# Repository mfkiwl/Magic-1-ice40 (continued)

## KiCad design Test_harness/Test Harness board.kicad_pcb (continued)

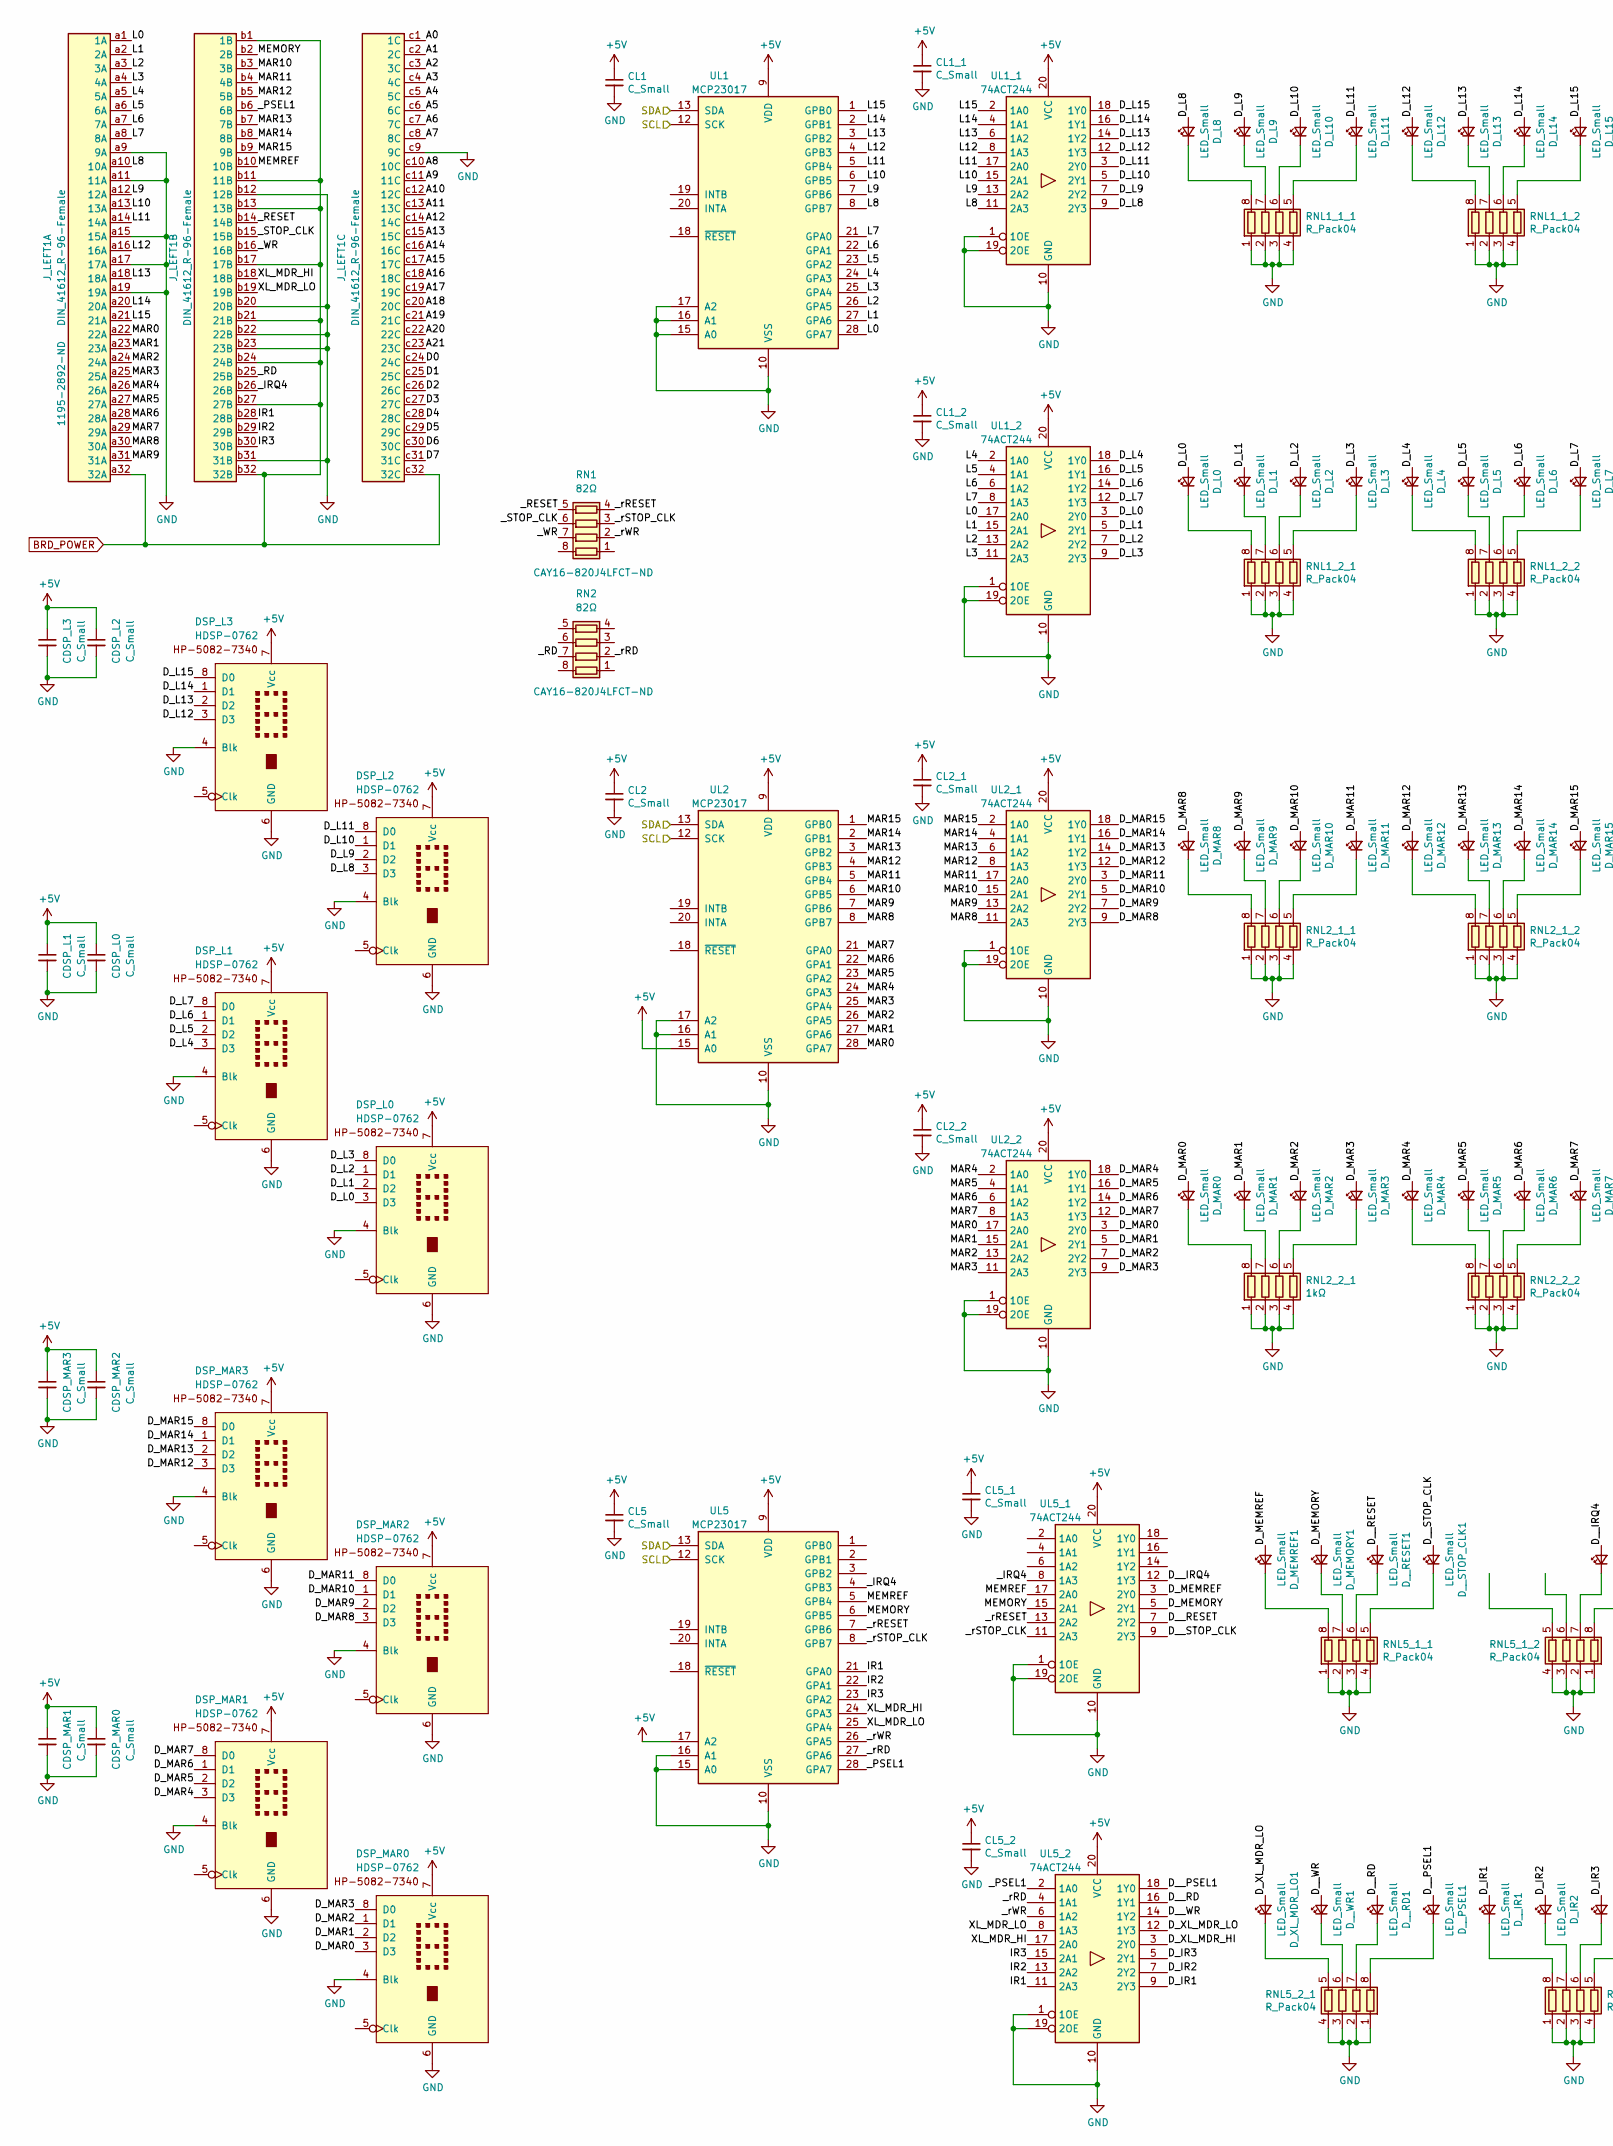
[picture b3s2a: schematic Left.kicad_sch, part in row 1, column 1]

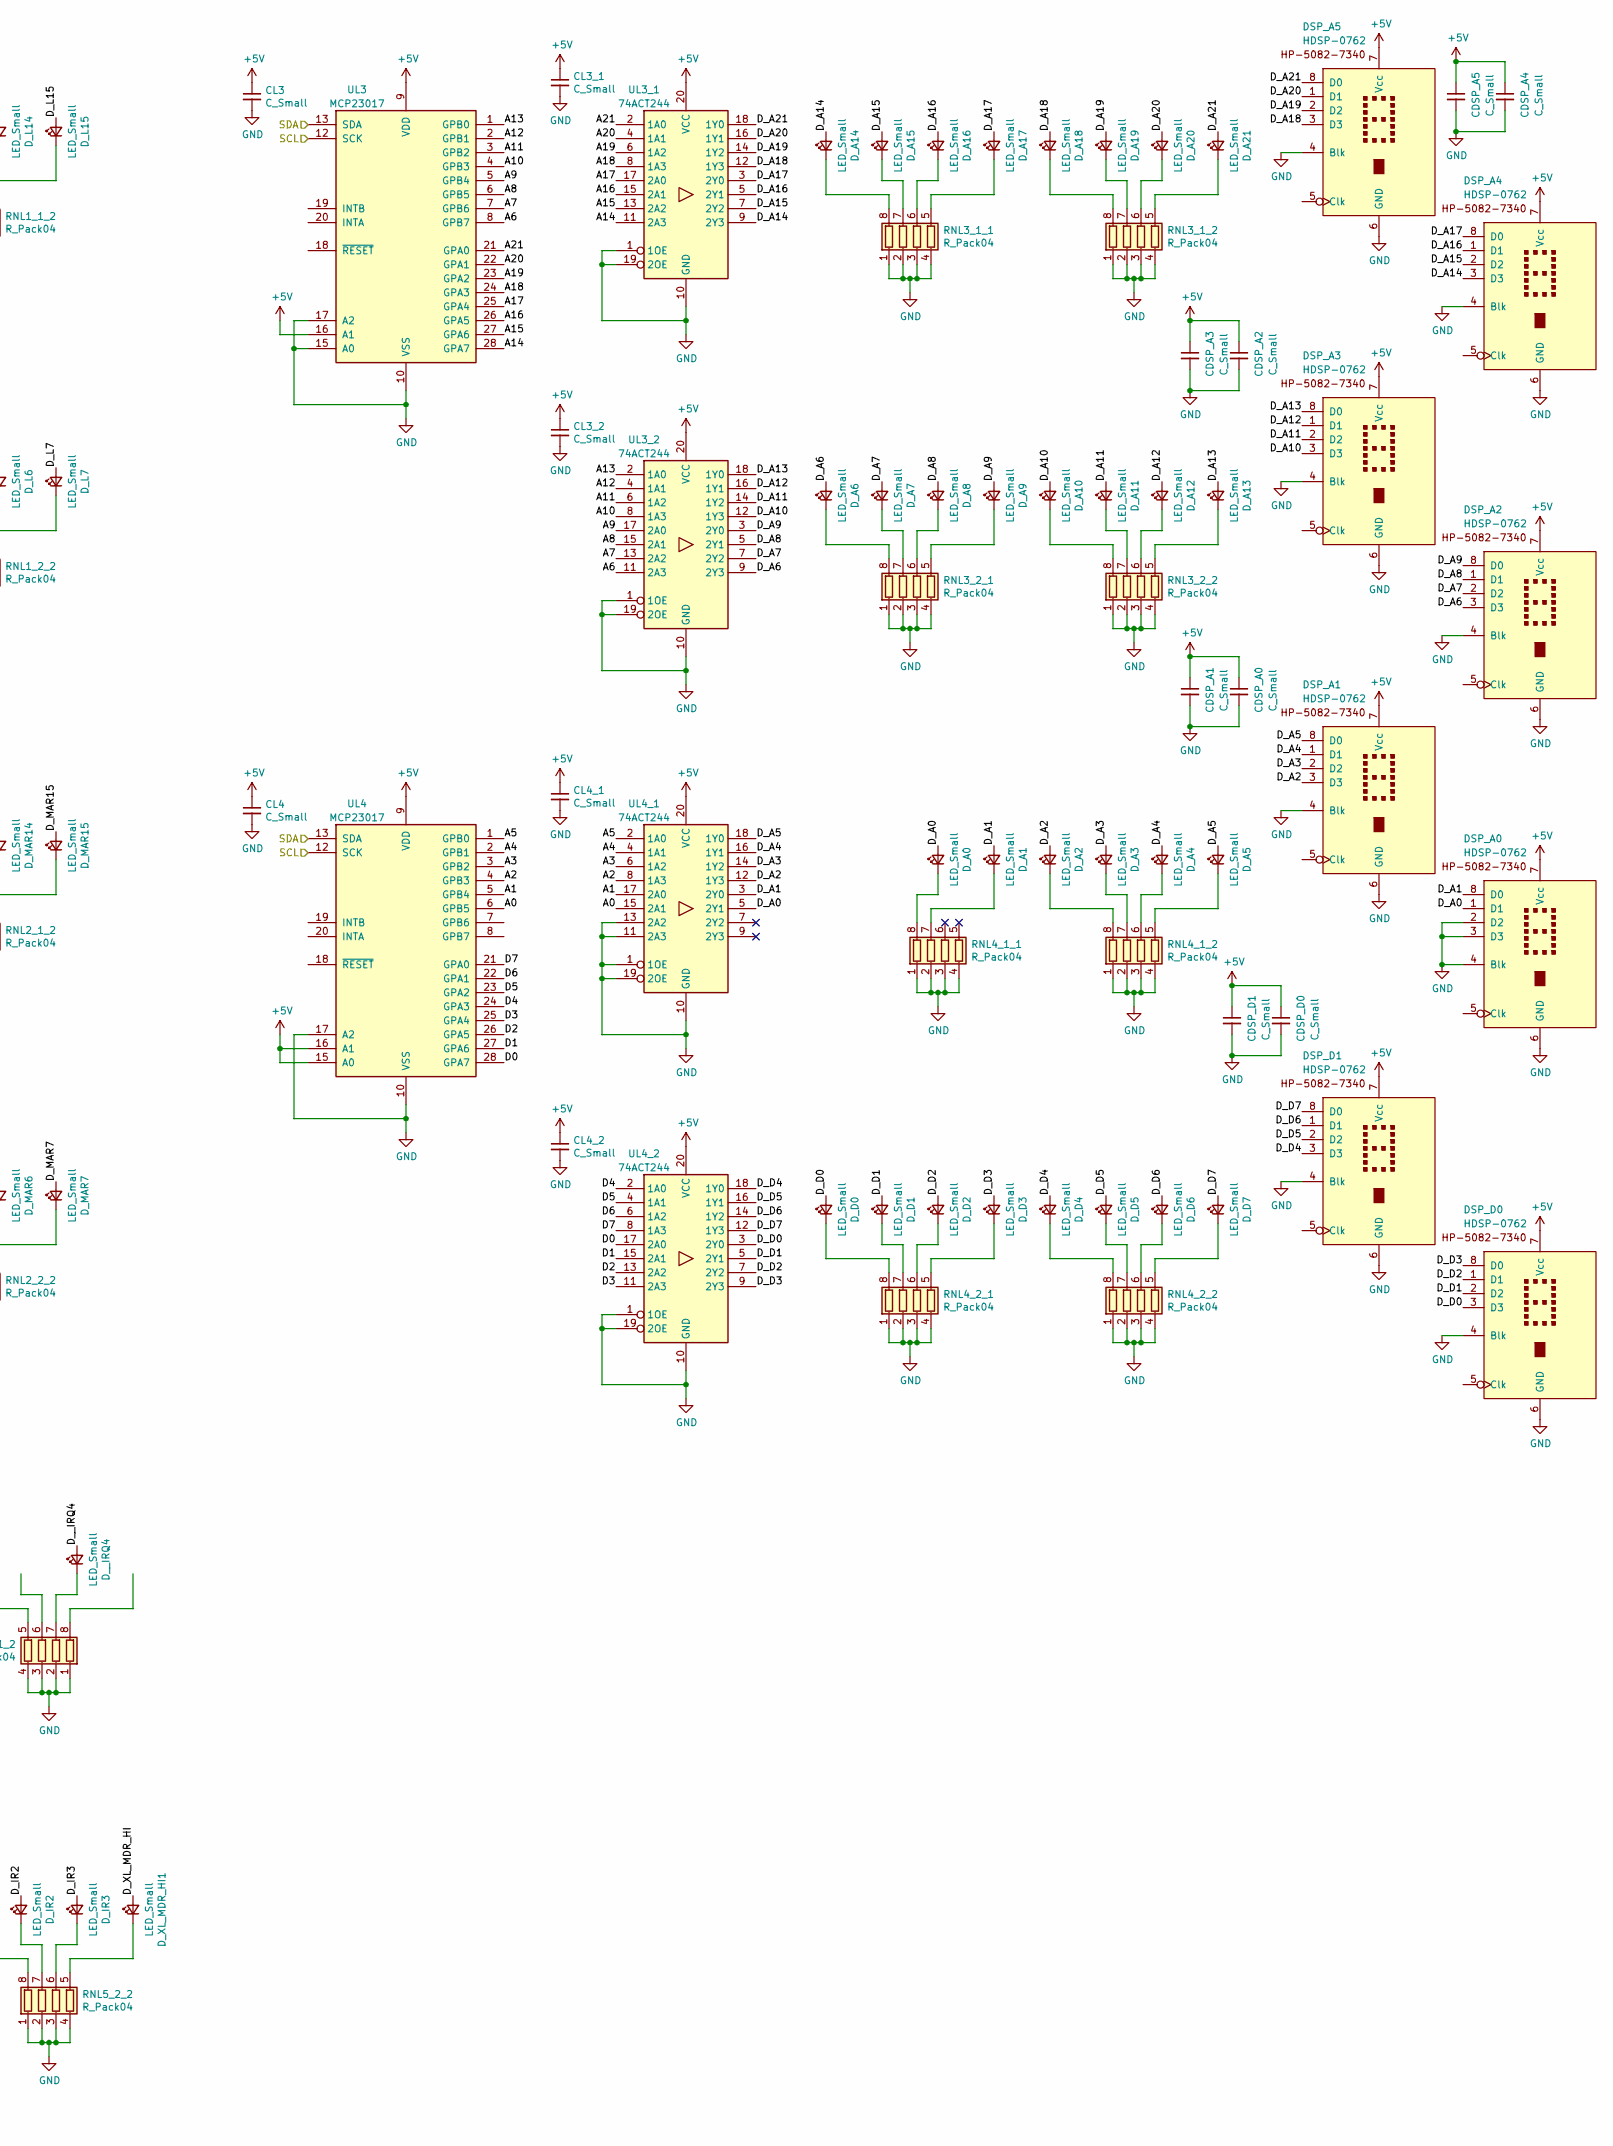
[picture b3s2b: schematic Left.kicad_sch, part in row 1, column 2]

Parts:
CDSP_A0, CDSP_A1, CDSP_A2, CDSP_A3, CDSP_A4, CDSP_A5: C_Small; C_0805_2012Metric
CDSP_D0, CDSP_D1: C_Small; C_0805_2012Metric
CDSP_L0, CDSP_L1, CDSP_L2, CDSP_L3: C_Small; C_0805_2012Metric
CDSP_MAR0, CDSP_MAR1, CDSP_MAR2, CDSP_MAR3: C_Small; C_0805_2012Metric
CL1, CL1_1, CL1_2, CL2, CL2_1, CL2_2, CL3, CL3_1, CL3_2, CL4, CL4_1, CL4_2, CL5, CL5_1, CL5_2: C_Small; C_0805_2012Metric
DSP_A0, DSP_A1, DSP_A2, DSP_A3, DSP_A4, DSP_A5: HDSP-0762; HDSP-076x-077x-086x-096x
DSP_D0, DSP_D1: HDSP-0762; HDSP-076x-077x-086x-096x
DSP_L0, DSP_L1, DSP_L2, DSP_L3: HDSP-0762; HDSP-076x-077x-086x-096x
DSP_MAR0, DSP_MAR1, DSP_MAR2, DSP_MAR3: HDSP-0762; HDSP-076x-077x-086x-096x
D_A0, D_A1, D_A2, D_A3, D_A4, D_A5, D_A6, D_A7, D_A8, D_A9, D_A10, D_A11, D_A12, D_A13, D_A14, D_A15, D_A16, D_A17, D_A18, D_A19, D_A20, D_A21: LED_Small; LED_0805_2012Metric; Digikey 160-1167-1-ND
D_D0, D_D1, D_D2, D_D3, D_D4, D_D5, D_D6, D_D7: LED_Small; LED_0805_2012Metric; Digikey 160-1167-1-ND
D_IR2, D_IR3: LED_Small; LED_0805_2012Metric; Digikey 160-1167-1-ND
D_L0, D_L1, D_L2, D_L3, D_L4, D_L5, D_L6, D_L7, D_L8, D_L9, D_L10, D_L11, D_L12, D_L13, D_L14, D_L15: LED_Small; LED_0805_2012Metric; Digikey 160-1167-1-ND
D_MAR0, D_MAR1, D_MAR2, D_MAR3, D_MAR4, D_MAR5, D_MAR6, D_MAR7, D_MAR8, D_MAR9, D_MAR10, D_MAR11, D_MAR12, D_MAR13, D_MAR14, D_MAR15: LED_Small; LED_0805_2012Metric; Digikey 160-1167-1-ND
D_MEMORY1: LED_Small; LED_0805_2012Metric; Digikey 160-1167-1-ND
D_MEMREF1: LED_Small; LED_0805_2012Metric; Digikey 160-1167-1-ND
D_XL_MDR_HI1: LED_Small; LED_0805_2012Metric; Digikey 160-1167-1-ND
D_XL_MDR_LO1: LED_Small; LED_0805_2012Metric; Digikey 160-1167-1-ND
D__IR1: LED_Small; LED_0805_2012Metric; Digikey 160-1167-1-ND
D__IRQ4: LED_Small; LED_0805_2012Metric; Digikey 160-1167-1-ND
D__PSEL1: LED_Small; LED_0805_2012Metric; Digikey 160-1167-1-ND
D__RD1: LED_Small; LED_0805_2012Metric; Digikey 160-1167-1-ND
D__RESET1: LED_Small; LED_0805_2012Metric; Digikey 160-1167-1-ND
D__STOP_CLK1: LED_Small; LED_0805_2012Metric; Digikey 160-1167-1-ND
D__WR1: LED_Small; LED_0805_2012Metric; Digikey 160-1167-1-ND
J_LEFT1: DIN_41612_R-96-Female; DIN41612_C_3x32_Male_Horizontal_THT; Digikey 1195-2892-ND
RN1, RN2: 82Ω; R_Array_Convex_4x1206; Digikey CAY16-820J4LFCT-ND
RNL1_1_1, RNL1_1_2, RNL1_2_1, RNL1_2_2, RNL2_1_1, RNL2_1_2, RNL2_2_2, RNL3_1_1, RNL3_1_2, RNL3_2_1, RNL3_2_2, RNL4_1_1, RNL4_1_2, RNL4_2_1, RNL4_2_2, RNL5_1_1, RNL5_1_2, RNL5_2_1, RNL5_2_2: R_Pack04; R_Array_Convex_4x1206; Digikey CAY16-331J4LFCT-ND
RNL2_2_1: 1kΩ; R_Array_Convex_4x1206; Digikey CAY16-331J4LFCT-ND
UL1, UL2, UL3, UL4, UL5: MCP23017; TSSOP-28_4.4x9.7mm_P0.65mm
UL1_1, UL1_2, UL2_1, UL2_2, UL3_1, UL3_2, UL4_1, UL4_2, UL5_1, UL5_2: 74ACT244; TSSOP-20_4.4x6.5mm_P0.65mm; Digikey 296-1071-1-ND

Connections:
+5V: CDSP_A0.1, CDSP_A1.1, CDSP_A2.1, CDSP_A3.1, CDSP_A4.1, CDSP_A5.1, CDSP_D0.1, CDSP_D1.1, CDSP_L0.1, CDSP_L1.1, CDSP_L2.1, CDSP_L3.1, CDSP_MAR0.1, CDSP_MAR1.1, CDSP_MAR2.1, CDSP_MAR3.1, CL1.1, CL1_1.1, CL1_2.1, CL2.1, CL2_1.1, CL2_2.1, CL3.1, CL3_1.1, CL3_2.1, CL4.1, CL4_1.1, CL4_2.1, CL5.1, CL5_1.1, CL5_2.1, DSP_A0.7 (Vcc), DSP_A1.7 (Vcc), DSP_A2.7 (Vcc), DSP_A3.7 (Vcc), DSP_A4.7 (Vcc), DSP_A5.7 (Vcc), DSP_D0.7 (Vcc), DSP_D1.7 (Vcc), DSP_L0.7 (Vcc), DSP_L1.7 (Vcc), DSP_L2.7 (Vcc), DSP_L3.7 (Vcc), DSP_MAR0.7 (Vcc), DSP_MAR1.7 (Vcc), DSP_MAR2.7 (Vcc), DSP_MAR3.7 (Vcc), UL1.9 (VDD), UL1_1.20 (VCC), UL1_2.20 (VCC), UL2.9 (VDD), UL2.15 (A0), UL2_1.20 (VCC), UL2_2.20 (VCC), UL3.9 (VDD), UL3.16 (A1), UL3_1.20 (VCC), UL3_2.20 (VCC), UL4.9 (VDD), UL4.15 (A0), UL4.16 (A1), UL4_1.20 (VCC), UL4_2.20 (VCC), UL5.9 (VDD), UL5.17 (A2), UL5_1.20 (VCC), UL5_2.20 (VCC); also elsewhere on the board
/Left connector/A0: J_LEFT1.c1 (1C), UL4.6 (GPB5), UL4_1.15 (2A1)
/Left connector/A1: J_LEFT1.c2 (2C), UL4.5 (GPB4), UL4_1.17 (2A0)
/Left connector/A2: J_LEFT1.c3 (3C), UL4.4 (GPB3), UL4_1.8 (1A3)
/Left connector/A3: J_LEFT1.c4 (4C), UL4.3 (GPB2), UL4_1.6 (1A2)
/Left connector/A4: J_LEFT1.c5 (5C), UL4.2 (GPB1), UL4_1.4 (1A1)
/Left connector/A5: J_LEFT1.c6 (6C), UL4.1 (GPB0), UL4_1.2 (1A0)
/Left connector/A6: J_LEFT1.c7 (7C), UL3.8 (GPB7), UL3_2.11 (2A3)
/Left connector/A7: J_LEFT1.c8 (8C), UL3.7 (GPB6), UL3_2.13 (2A2)
/Left connector/A8: J_LEFT1.c10 (10C), UL3.6 (GPB5), UL3_2.15 (2A1)
/Left connector/A9: J_LEFT1.c11 (11C), UL3.5 (GPB4), UL3_2.17 (2A0)
/Left connector/A10: J_LEFT1.c12 (12C), UL3.4 (GPB3), UL3_2.8 (1A3)
/Left connector/A11: J_LEFT1.c13 (13C), UL3.3 (GPB2), UL3_2.6 (1A2)
/Left connector/A12: J_LEFT1.c14 (14C), UL3.2 (GPB1), UL3_2.4 (1A1)
/Left connector/A13: J_LEFT1.c15 (15C), UL3.1 (GPB0), UL3_2.2 (1A0)
/Left connector/A14: J_LEFT1.c16 (16C), UL3.28 (GPA7), UL3_1.11 (2A3)
/Left connector/A15: J_LEFT1.c17 (17C), UL3.27 (GPA6), UL3_1.13 (2A2)
/Left connector/A16: J_LEFT1.c18 (18C), UL3.26 (GPA5), UL3_1.15 (2A1)
/Left connector/A17: J_LEFT1.c19 (19C), UL3.25 (GPA4), UL3_1.17 (2A0)
/Left connector/A18: J_LEFT1.c20 (20C), UL3.24 (GPA3), UL3_1.8 (1A3)
/Left connector/A19: J_LEFT1.c21 (21C), UL3.23 (GPA2), UL3_1.6 (1A2)
/Left connector/A20: J_LEFT1.c22 (22C), UL3.22 (GPA1), UL3_1.4 (1A1)
/Left connector/A21: J_LEFT1.c23 (23C), UL3.21 (GPA0), UL3_1.2 (1A0)
/Left connector/D0: J_LEFT1.c24 (24C), UL4.28 (GPA7), UL4_2.17 (2A0)
/Left connector/D1: J_LEFT1.c25 (25C), UL4.27 (GPA6), UL4_2.15 (2A1)
/Left connector/D2: J_LEFT1.c26 (26C), UL4.26 (GPA5), UL4_2.13 (2A2)
/Left connector/D3: J_LEFT1.c27 (27C), UL4.25 (GPA4), UL4_2.11 (2A3)
/Left connector/D4: J_LEFT1.c28 (28C), UL4.24 (GPA3), UL4_2.2 (1A0)
/Left connector/D5: J_LEFT1.c29 (29C), UL4.23 (GPA2), UL4_2.4 (1A1)
/Left connector/D6: J_LEFT1.c30 (30C), UL4.22 (GPA1), UL4_2.6 (1A2)
/Left connector/D7: J_LEFT1.c31 (31C), UL4.21 (GPA0), UL4_2.8 (1A3)
/Left connector/D_A0: DSP_A0.1 (D1), D_A0.2 (A), UL4_1.5 (2Y1)
/Left connector/D_A1: DSP_A0.8 (D0), D_A1.2 (A), UL4_1.3 (2Y0)
/Left connector/D_A2: DSP_A1.3 (D3), D_A2.2 (A), UL4_1.12 (1Y3)
/Left connector/D_A3: DSP_A1.2 (D2), D_A3.2 (A), UL4_1.14 (1Y2)
/Left connector/D_A4: DSP_A1.1 (D1), D_A4.2 (A), UL4_1.16 (1Y1)
/Left connector/D_A5: DSP_A1.8 (D0), D_A5.2 (A), UL4_1.18 (1Y0)
/Left connector/D_A6: DSP_A2.3 (D3), D_A6.2 (A), UL3_2.9 (2Y3)
/Left connector/D_A7: DSP_A2.2 (D2), D_A7.2 (A), UL3_2.7 (2Y2)
/Left connector/D_A8: DSP_A2.1 (D1), D_A8.2 (A), UL3_2.5 (2Y1)
/Left connector/D_A9: DSP_A2.8 (D0), D_A9.2 (A), UL3_2.3 (2Y0)
/Left connector/D_A10: DSP_A3.3 (D3), D_A10.2 (A), UL3_2.12 (1Y3)
/Left connector/D_A11: DSP_A3.2 (D2), D_A11.2 (A), UL3_2.14 (1Y2)
/Left connector/D_A12: DSP_A3.1 (D1), D_A12.2 (A), UL3_2.16 (1Y1)
/Left connector/D_A13: DSP_A3.8 (D0), D_A13.2 (A), UL3_2.18 (1Y0)
/Left connector/D_A14: DSP_A4.3 (D3), D_A14.2 (A), UL3_1.9 (2Y3)
/Left connector/D_A15: DSP_A4.2 (D2), D_A15.2 (A), UL3_1.7 (2Y2)
/Left connector/D_A16: DSP_A4.1 (D1), D_A16.2 (A), UL3_1.5 (2Y1)
/Left connector/D_A17: DSP_A4.8 (D0), D_A17.2 (A), UL3_1.3 (2Y0)
/Left connector/D_A18: DSP_A5.3 (D3), D_A18.2 (A), UL3_1.12 (1Y3)
/Left connector/D_A19: DSP_A5.2 (D2), D_A19.2 (A), UL3_1.14 (1Y2)
/Left connector/D_A20: DSP_A5.1 (D1), D_A20.2 (A), UL3_1.16 (1Y1)
/Left connector/D_A21: DSP_A5.8 (D0), D_A21.2 (A), UL3_1.18 (1Y0)
/Left connector/D_D0: DSP_D0.3 (D3), D_D0.2 (A), UL4_2.3 (2Y0)
/Left connector/D_D1: DSP_D0.2 (D2), D_D1.2 (A), UL4_2.5 (2Y1)
/Left connector/D_D2: DSP_D0.1 (D1), D_D2.2 (A), UL4_2.7 (2Y2)
/Left connector/D_D3: DSP_D0.8 (D0), D_D3.2 (A), UL4_2.9 (2Y3)
/Left connector/D_D4: DSP_D1.3 (D3), D_D4.2 (A), UL4_2.18 (1Y0)
/Left connector/D_D5: DSP_D1.2 (D2), D_D5.2 (A), UL4_2.16 (1Y1)
/Left connector/D_D6: DSP_D1.1 (D1), D_D6.2 (A), UL4_2.14 (1Y2)
/Left connector/D_D7: DSP_D1.8 (D0), D_D7.2 (A), UL4_2.12 (1Y3)
/Left connector/D_IR1: D__IR1.2 (A), UL5_2.9 (2Y3)
/Left connector/D_IR2: D_IR2.2 (A), UL5_2.7 (2Y2)
/Left connector/D_IR3: D_IR3.2 (A), UL5_2.5 (2Y1)
/Left connector/D_L0: DSP_L0.3 (D3), D_L0.2 (A), UL1_2.3 (2Y0)
/Left connector/D_L1: DSP_L0.2 (D2), D_L1.2 (A), UL1_2.5 (2Y1)
/Left connector/D_L2: DSP_L0.1 (D1), D_L2.2 (A), UL1_2.7 (2Y2)
/Left connector/D_L3: DSP_L0.8 (D0), D_L3.2 (A), UL1_2.9 (2Y3)
/Left connector/D_L4: DSP_L1.3 (D3), D_L4.2 (A), UL1_2.18 (1Y0)
/Left connector/D_L5: DSP_L1.2 (D2), D_L5.2 (A), UL1_2.16 (1Y1)
/Left connector/D_L6: DSP_L1.1 (D1), D_L6.2 (A), UL1_2.14 (1Y2)
/Left connector/D_L7: DSP_L1.8 (D0), D_L7.2 (A), UL1_2.12 (1Y3)
/Left connector/D_L8: DSP_L2.3 (D3), D_L8.2 (A), UL1_1.9 (2Y3)
/Left connector/D_L9: DSP_L2.2 (D2), D_L9.2 (A), UL1_1.7 (2Y2)
/Left connector/D_L10: DSP_L2.1 (D1), D_L10.2 (A), UL1_1.5 (2Y1)
/Left connector/D_L11: DSP_L2.8 (D0), D_L11.2 (A), UL1_1.3 (2Y0)
/Left connector/D_L12: DSP_L3.3 (D3), D_L12.2 (A), UL1_1.12 (1Y3)
/Left connector/D_L13: DSP_L3.2 (D2), D_L13.2 (A), UL1_1.14 (1Y2)
/Left connector/D_L14: DSP_L3.1 (D1), D_L14.2 (A), UL1_1.16 (1Y1)
/Left connector/D_L15: DSP_L3.8 (D0), D_L15.2 (A), UL1_1.18 (1Y0)
/Left connector/D_MAR0: DSP_MAR0.3 (D3), D_MAR0.2 (A), UL2_2.3 (2Y0)
/Left connector/D_MAR1: DSP_MAR0.2 (D2), D_MAR1.2 (A), UL2_2.5 (2Y1)
/Left connector/D_MAR2: DSP_MAR0.1 (D1), D_MAR2.2 (A), UL2_2.7 (2Y2)
/Left connector/D_MAR3: DSP_MAR0.8 (D0), D_MAR3.2 (A), UL2_2.9 (2Y3)
/Left connector/D_MAR4: DSP_MAR1.3 (D3), D_MAR4.2 (A), UL2_2.18 (1Y0)
/Left connector/D_MAR5: DSP_MAR1.2 (D2), D_MAR5.2 (A), UL2_2.16 (1Y1)
/Left connector/D_MAR6: DSP_MAR1.1 (D1), D_MAR6.2 (A), UL2_2.14 (1Y2)
/Left connector/D_MAR7: DSP_MAR1.8 (D0), D_MAR7.2 (A), UL2_2.12 (1Y3)
/Left connector/D_MAR8: DSP_MAR2.3 (D3), D_MAR8.2 (A), UL2_1.9 (2Y3)
/Left connector/D_MAR9: DSP_MAR2.2 (D2), D_MAR9.2 (A), UL2_1.7 (2Y2)
/Left connector/D_MAR10: DSP_MAR2.1 (D1), D_MAR10.2 (A), UL2_1.5 (2Y1)
/Left connector/D_MAR11: DSP_MAR2.8 (D0), D_MAR11.2 (A), UL2_1.3 (2Y0)
/Left connector/D_MAR12: DSP_MAR3.3 (D3), D_MAR12.2 (A), UL2_1.12 (1Y3)
/Left connector/D_MAR13: DSP_MAR3.2 (D2), D_MAR13.2 (A), UL2_1.14 (1Y2)
/Left connector/D_MAR14: DSP_MAR3.1 (D1), D_MAR14.2 (A), UL2_1.16 (1Y1)
/Left connector/D_MAR15: DSP_MAR3.8 (D0), D_MAR15.2 (A), UL2_1.18 (1Y0)
/Left connector/D_MEMORY: D_MEMORY1.2 (A), UL5_1.5 (2Y1)
/Left connector/D_MEMREF: D_MEMREF1.2 (A), UL5_1.3 (2Y0)
/Left connector/D_XL_MDR_HI: D_XL_MDR_HI1.2 (A), UL5_2.3 (2Y0)
/Left connector/D_XL_MDR_LO: D_XL_MDR_LO1.2 (A), UL5_2.12 (1Y3)
/Left connector/D__IRQ4: D__IRQ4.2 (A), UL5_1.12 (1Y3)
/Left connector/D__PSEL1: D__PSEL1.2 (A), UL5_2.18 (1Y0)
/Left connector/D__RD: D__RD1.2 (A), UL5_2.16 (1Y1)
/Left connector/D__RESET: D__RESET1.2 (A), UL5_1.7 (2Y2)
/Left connector/D__STOP_CLK: D__STOP_CLK1.2 (A), UL5_1.9 (2Y3)
/Left connector/D__WR: D__WR1.2 (A), UL5_2.14 (1Y2)
/Left connector/IR1: J_LEFT1.b28 (28B), UL5.21 (GPA0), UL5_2.11 (2A3)
/Left connector/IR2: J_LEFT1.b29 (29B), UL5.22 (GPA1), UL5_2.13 (2A2)
/Left connector/IR3: J_LEFT1.b30 (30B), UL5.23 (GPA2), UL5_2.15 (2A1)
/Left connector/L0: J_LEFT1.a1 (1A), UL1.28 (GPA7), UL1_2.17 (2A0)
/Left connector/L1: J_LEFT1.a2 (2A), UL1.27 (GPA6), UL1_2.15 (2A1)
/Left connector/L2: J_LEFT1.a3 (3A), UL1.26 (GPA5), UL1_2.13 (2A2)
/Left connector/L3: J_LEFT1.a4 (4A), UL1.25 (GPA4), UL1_2.11 (2A3)
/Left connector/L4: J_LEFT1.a5 (5A), UL1.24 (GPA3), UL1_2.2 (1A0)
/Left connector/L5: J_LEFT1.a6 (6A), UL1.23 (GPA2), UL1_2.4 (1A1)
/Left connector/L6: J_LEFT1.a7 (7A), UL1.22 (GPA1), UL1_2.6 (1A2)
/Left connector/L7: J_LEFT1.a8 (8A), UL1.21 (GPA0), UL1_2.8 (1A3)
/Left connector/L8: J_LEFT1.a10 (10A), UL1.8 (GPB7), UL1_1.11 (2A3)
/Left connector/L9: J_LEFT1.a12 (12A), UL1.7 (GPB6), UL1_1.13 (2A2)
/Left connector/L10: J_LEFT1.a13 (13A), UL1.6 (GPB5), UL1_1.15 (2A1)
/Left connector/L11: J_LEFT1.a14 (14A), UL1.5 (GPB4), UL1_1.17 (2A0)
/Left connector/L12: J_LEFT1.a16 (16A), UL1.4 (GPB3), UL1_1.8 (1A3)
/Left connector/L13: J_LEFT1.a18 (18A), UL1.3 (GPB2), UL1_1.6 (1A2)
/Left connector/L14: J_LEFT1.a20 (20A), UL1.2 (GPB1), UL1_1.4 (1A1)
/Left connector/L15: J_LEFT1.a21 (21A), UL1.1 (GPB0), UL1_1.2 (1A0)
/Left connector/MAR0: J_LEFT1.a22 (22A), UL2.28 (GPA7), UL2_2.17 (2A0)
/Left connector/MAR1: J_LEFT1.a23 (23A), UL2.27 (GPA6), UL2_2.15 (2A1)
/Left connector/MAR2: J_LEFT1.a24 (24A), UL2.26 (GPA5), UL2_2.13 (2A2)
/Left connector/MAR3: J_LEFT1.a25 (25A), UL2.25 (GPA4), UL2_2.11 (2A3)
/Left connector/MAR4: J_LEFT1.a26 (26A), UL2.24 (GPA3), UL2_2.2 (1A0)
/Left connector/MAR5: J_LEFT1.a27 (27A), UL2.23 (GPA2), UL2_2.4 (1A1)
/Left connector/MAR6: J_LEFT1.a28 (28A), UL2.22 (GPA1), UL2_2.6 (1A2)
/Left connector/MAR7: J_LEFT1.a29 (29A), UL2.21 (GPA0), UL2_2.8 (1A3)
/Left connector/MAR8: J_LEFT1.a30 (30A), UL2.8 (GPB7), UL2_1.11 (2A3)
/Left connector/MAR9: J_LEFT1.a31 (31A), UL2.7 (GPB6), UL2_1.13 (2A2)
/Left connector/MAR10: J_LEFT1.b3 (3B), UL2.6 (GPB5), UL2_1.15 (2A1)
/Left connector/MAR11: J_LEFT1.b4 (4B), UL2.5 (GPB4), UL2_1.17 (2A0)
/Left connector/MAR12: J_LEFT1.b5 (5B), UL2.4 (GPB3), UL2_1.8 (1A3)
/Left connector/MAR13: J_LEFT1.b7 (7B), UL2.3 (GPB2), UL2_1.6 (1A2)
/Left connector/MAR14: J_LEFT1.b8 (8B), UL2.2 (GPB1), UL2_1.4 (1A1)
/Left connector/MAR15: J_LEFT1.b9 (9B), UL2.1 (GPB0), UL2_1.2 (1A0)
/Left connector/MEMORY: J_LEFT1.b2 (2B), UL5.6 (GPB5), UL5_1.15 (2A1)
/Left connector/MEMREF: J_LEFT1.b10 (10B), UL5.5 (GPB4), UL5_1.17 (2A0)
/Left connector/XL_MDR_HI: J_LEFT1.b18 (18B), UL5.24 (GPA3), UL5_2.17 (2A0)
/Left connector/XL_MDR_LO: J_LEFT1.b19 (19B), UL5.25 (GPA4), UL5_2.8 (1A3)
/Left connector/_IRQ4: J_LEFT1.b26 (26B), UL5.4 (GPB3), UL5_1.8 (1A3)
/Left connector/_PSEL1: J_LEFT1.b6 (6B), UL5.28 (GPA7), UL5_2.2 (1A0)
/Left connector/_RD: J_LEFT1.b25 (25B), RN2.7 (R2.2)
/Left connector/_RESET: J_LEFT1.b14 (14B), RN1.5 (R4.2)
/Left connector/_STOP_CLK: J_LEFT1.b15 (15B), RN1.6 (R3.2)
/Left connector/_WR: J_LEFT1.b16 (16B), RN1.7 (R2.2)
/Left connector/_rRD: RN2.2 (R2.1), UL5.27 (GPA6), UL5_2.4 (1A1)
/Left connector/_rRESET: RN1.4 (R4.1), UL5.7 (GPB6), UL5_1.13 (2A2)
/Left connector/_rSTOP_CLK: RN1.3 (R3.1), UL5.8 (GPB7), UL5_1.11 (2A3)
/Left connector/_rWR: RN1.2 (R2.1), UL5.26 (GPA5), UL5_2.6 (1A2)
/SCL_0: UL1.12 (SCK), UL2.12 (SCK), UL3.12 (SCK), UL4.12 (SCK), UL5.12 (SCK); also elsewhere on the board
/SDA_0: UL1.13 (SDA), UL2.13 (SDA), UL3.13 (SDA), UL4.13 (SDA), UL5.13 (SDA); also elsewhere on the board
BRD_POWER: J_LEFT1.a32 (32A), J_LEFT1.b1 (1B), J_LEFT1.b11 (11B), J_LEFT1.b13 (13B), J_LEFT1.b17 (17B), J_LEFT1.b21 (21B), J_LEFT1.b24 (24B), J_LEFT1.b27 (27B), J_LEFT1.b32 (32B), J_LEFT1.c32 (32C); also elsewhere on the board
GND: CDSP_A0.2, CDSP_A1.2, CDSP_A2.2, CDSP_A3.2, CDSP_A4.2, CDSP_A5.2, CDSP_D0.2, CDSP_D1.2, CDSP_L0.2, CDSP_L1.2, CDSP_L2.2, CDSP_L3.2, CDSP_MAR0.2, CDSP_MAR1.2, CDSP_MAR2.2, CDSP_MAR3.2, CL1.2, CL1_1.2, CL1_2.2, CL2.2, CL2_1.2, CL2_2.2, CL3.2, CL3_1.2, CL3_2.2, CL4.2, CL4_1.2, CL4_2.2, CL5.2, CL5_1.2, CL5_2.2, DSP_A0.2 (D2), DSP_A0.3 (D3), DSP_A0.4 (Blk), DSP_A0.6 (GND), DSP_A1.4 (Blk), DSP_A1.6 (GND), DSP_A2.4 (Blk), DSP_A2.6 (GND), DSP_A3.4 (Blk), DSP_A3.6 (GND), DSP_A4.4 (Blk), DSP_A4.6 (GND), DSP_A5.4 (Blk), DSP_A5.6 (GND), DSP_D0.4 (Blk), DSP_D0.6 (GND), DSP_D1.4 (Blk), DSP_D1.6 (GND), DSP_L0.4 (Blk), DSP_L0.6 (GND), DSP_L1.4 (Blk), DSP_L1.6 (GND), DSP_L2.4 (Blk), DSP_L2.6 (GND), DSP_L3.4 (Blk), DSP_L3.6 (GND), DSP_MAR0.4 (Blk), DSP_MAR0.6 (GND), DSP_MAR1.4 (Blk), DSP_MAR1.6 (GND), DSP_MAR2.4 (Blk), DSP_MAR2.6 (GND), DSP_MAR3.4 (Blk), DSP_MAR3.6 (GND), J_LEFT1.a9 (9A), J_LEFT1.a11 (11A), J_LEFT1.a15 (15A), J_LEFT1.a17 (17A), J_LEFT1.a19 (19A), J_LEFT1.b12 (12B), J_LEFT1.b20 (20B), J_LEFT1.b22 (22B), J_LEFT1.b23 (23B), J_LEFT1.b31 (31B), J_LEFT1.c9 (9C), RNL1_1_1.1 (R1.1), RNL1_1_1.2 (R2.1), RNL1_1_1.3 (R3.1), RNL1_1_1.4 (R4.1), RNL1_1_2.1 (R1.1), RNL1_1_2.2 (R2.1), RNL1_1_2.3 (R3.1), RNL1_1_2.4 (R4.1), RNL1_2_1.1 (R1.1), RNL1_2_1.2 (R2.1), RNL1_2_1.3 (R3.1), RNL1_2_1.4 (R4.1), RNL1_2_2.1 (R1.1), RNL1_2_2.2 (R2.1), RNL1_2_2.3 (R3.1), RNL1_2_2.4 (R4.1), RNL2_1_1.1 (R1.1), RNL2_1_1.2 (R2.1), RNL2_1_1.3 (R3.1), RNL2_1_1.4 (R4.1), RNL2_1_2.1 (R1.1), RNL2_1_2.2 (R2.1), RNL2_1_2.3 (R3.1), RNL2_1_2.4 (R4.1), RNL2_2_1.1 (R1.1), RNL2_2_1.2 (R2.1), RNL2_2_1.3 (R3.1), RNL2_2_1.4 (R4.1), RNL2_2_2.1 (R1.1), RNL2_2_2.2 (R2.1), RNL2_2_2.3 (R3.1), RNL2_2_2.4 (R4.1), RNL3_1_1.1 (R1.1), RNL3_1_1.2 (R2.1), RNL3_1_1.3 (R3.1), RNL3_1_1.4 (R4.1), RNL3_1_2.1 (R1.1), RNL3_1_2.2 (R2.1), RNL3_1_2.3 (R3.1), RNL3_1_2.4 (R4.1), RNL3_2_1.1 (R1.1), RNL3_2_1.2 (R2.1), RNL3_2_1.3 (R3.1), RNL3_2_1.4 (R4.1), RNL3_2_2.1 (R1.1), RNL3_2_2.2 (R2.1), RNL3_2_2.3 (R3.1), RNL3_2_2.4 (R4.1), RNL4_1_1.1 (R1.1), RNL4_1_1.2 (R2.1), RNL4_1_1.3 (R3.1), RNL4_1_1.4 (R4.1), RNL4_1_2.1 (R1.1), RNL4_1_2.2 (R2.1), RNL4_1_2.3 (R3.1), RNL4_1_2.4 (R4.1), RNL4_2_1.1 (R1.1), RNL4_2_1.2 (R2.1), RNL4_2_1.3 (R3.1), RNL4_2_1.4 (R4.1), RNL4_2_2.1 (R1.1), RNL4_2_2.2 (R2.1), RNL4_2_2.3 (R3.1), RNL4_2_2.4 (R4.1), RNL5_1_1.1 (R1.1), RNL5_1_1.2 (R2.1), RNL5_1_1.3 (R3.1), RNL5_1_1.4 (R4.1), RNL5_1_2.1 (R1.1), RNL5_1_2.2 (R2.1), RNL5_1_2.3 (R3.1), RNL5_1_2.4 (R4.1), RNL5_2_1.1 (R1.1), RNL5_2_1.2 (R2.1), RNL5_2_1.3 (R3.1), RNL5_2_1.4 (R4.1), RNL5_2_2.1 (R1.1), RNL5_2_2.2 (R2.1), RNL5_2_2.3 (R3.1), RNL5_2_2.4 (R4.1), UL1.10 (VSS), UL1.15 (A0), UL1.16 (A1), UL1.17 (A2), UL1_1.1 (1OE), UL1_1.10 (GND), UL1_1.19 (2OE), UL1_2.1 (1OE), UL1_2.10 (GND), UL1_2.19 (2OE), UL2.10 (VSS), UL2.16 (A1), UL2.17 (A2), UL2_1.1 (1OE), UL2_1.10 (GND), UL2_1.19 (2OE), UL2_2.1 (1OE), UL2_2.10 (GND), UL2_2.19 (2OE), UL3.10 (VSS), UL3.15 (A0), UL3.17 (A2), UL3_1.1 (1OE), UL3_1.10 (GND), UL3_1.19 (2OE), UL3_2.1 (1OE), UL3_2.10 (GND), UL3_2.19 (2OE), UL4.10 (VSS), UL4.17 (A2), UL4_1.1 (1OE), UL4_1.10 (GND), UL4_1.11 (2A3), UL4_1.13 (2A2), UL4_1.19 (2OE), UL4_2.1 (1OE), UL4_2.10 (GND), UL4_2.19 (2OE), UL5.10 (VSS), UL5.15 (A0), UL5.16 (A1), UL5_1.1 (1OE), UL5_1.10 (GND), UL5_1.19 (2OE), UL5_2.1 (1OE), UL5_2.10 (GND), UL5_2.19 (2OE); also elsewhere on the board
unnamed: D_A0.1 (K), RNL4_1_1.8 (R1.2)
unnamed: D_A1.1 (K), RNL4_1_1.7 (R2.2)
unnamed: D_A2.1 (K), RNL4_1_2.8 (R1.2)
unnamed: D_A3.1 (K), RNL4_1_2.7 (R2.2)
unnamed: D_A4.1 (K), RNL4_1_2.6 (R3.2)
unnamed: D_A5.1 (K), RNL4_1_2.5 (R4.2)
unnamed: D_A6.1 (K), RNL3_2_1.8 (R1.2)
unnamed: D_A7.1 (K), RNL3_2_1.7 (R2.2)
unnamed: D_A8.1 (K), RNL3_2_1.6 (R3.2)
unnamed: D_A9.1 (K), RNL3_2_1.5 (R4.2)
unnamed: D_A10.1 (K), RNL3_2_2.8 (R1.2)
unnamed: D_A11.1 (K), RNL3_2_2.7 (R2.2)
unnamed: D_A12.1 (K), RNL3_2_2.6 (R3.2)
unnamed: D_A13.1 (K), RNL3_2_2.5 (R4.2)
unnamed: D_A14.1 (K), RNL3_1_1.8 (R1.2)
unnamed: D_A15.1 (K), RNL3_1_1.7 (R2.2)
unnamed: D_A16.1 (K), RNL3_1_1.6 (R3.2)
unnamed: D_A17.1 (K), RNL3_1_1.5 (R4.2)
unnamed: D_A18.1 (K), RNL3_1_2.8 (R1.2)
unnamed: D_A19.1 (K), RNL3_1_2.7 (R2.2)
unnamed: D_A20.1 (K), RNL3_1_2.6 (R3.2)
unnamed: D_A21.1 (K), RNL3_1_2.5 (R4.2)
unnamed: D_D0.1 (K), RNL4_2_1.8 (R1.2)
unnamed: D_D1.1 (K), RNL4_2_1.7 (R2.2)
unnamed: D_D2.1 (K), RNL4_2_1.6 (R3.2)
unnamed: D_D3.1 (K), RNL4_2_1.5 (R4.2)
unnamed: D_D4.1 (K), RNL4_2_2.8 (R1.2)
unnamed: D_D5.1 (K), RNL4_2_2.7 (R2.2)
unnamed: D_D6.1 (K), RNL4_2_2.6 (R3.2)
unnamed: D_D7.1 (K), RNL4_2_2.5 (R4.2)
unnamed: D_IR2.1 (K), RNL5_2_2.7 (R2.2)
unnamed: D_IR3.1 (K), RNL5_2_2.6 (R3.2)
unnamed: D_L0.1 (K), RNL1_2_1.8 (R1.2)
unnamed: D_L1.1 (K), RNL1_2_1.7 (R2.2)
unnamed: D_L2.1 (K), RNL1_2_1.6 (R3.2)
unnamed: D_L3.1 (K), RNL1_2_1.5 (R4.2)
unnamed: D_L4.1 (K), RNL1_2_2.8 (R1.2)
unnamed: D_L5.1 (K), RNL1_2_2.7 (R2.2)
unnamed: D_L6.1 (K), RNL1_2_2.6 (R3.2)
unnamed: D_L7.1 (K), RNL1_2_2.5 (R4.2)
unnamed: D_L8.1 (K), RNL1_1_1.8 (R1.2)
unnamed: D_L9.1 (K), RNL1_1_1.7 (R2.2)
unnamed: D_L10.1 (K), RNL1_1_1.6 (R3.2)
unnamed: D_L11.1 (K), RNL1_1_1.5 (R4.2)
unnamed: D_L12.1 (K), RNL1_1_2.8 (R1.2)
unnamed: D_L13.1 (K), RNL1_1_2.7 (R2.2)
unnamed: D_L14.1 (K), RNL1_1_2.6 (R3.2)
unnamed: D_L15.1 (K), RNL1_1_2.5 (R4.2)
unnamed: D_MAR0.1 (K), RNL2_2_1.8 (R1.2)
unnamed: D_MAR1.1 (K), RNL2_2_1.7 (R2.2)
unnamed: D_MAR2.1 (K), RNL2_2_1.6 (R3.2)
unnamed: D_MAR3.1 (K), RNL2_2_1.5 (R4.2)
unnamed: D_MAR4.1 (K), RNL2_2_2.8 (R1.2)
unnamed: D_MAR5.1 (K), RNL2_2_2.7 (R2.2)
unnamed: D_MAR6.1 (K), RNL2_2_2.6 (R3.2)
unnamed: D_MAR7.1 (K), RNL2_2_2.5 (R4.2)
unnamed: D_MAR8.1 (K), RNL2_1_1.8 (R1.2)
unnamed: D_MAR9.1 (K), RNL2_1_1.7 (R2.2)
unnamed: D_MAR10.1 (K), RNL2_1_1.6 (R3.2)
unnamed: D_MAR11.1 (K), RNL2_1_1.5 (R4.2)
unnamed: D_MAR12.1 (K), RNL2_1_2.8 (R1.2)
unnamed: D_MAR13.1 (K), RNL2_1_2.7 (R2.2)
unnamed: D_MAR14.1 (K), RNL2_1_2.6 (R3.2)
unnamed: D_MAR15.1 (K), RNL2_1_2.5 (R4.2)
unnamed: D_MEMORY1.1 (K), RNL5_1_1.7 (R2.2)
unnamed: D_MEMREF1.1 (K), RNL5_1_1.8 (R1.2)
unnamed: D_XL_MDR_HI1.1 (K), RNL5_2_2.5 (R4.2)
unnamed: D_XL_MDR_LO1.1 (K), RNL5_2_1.5 (R4.2)
unnamed: D__IR1.1 (K), RNL5_2_2.8 (R1.2)
unnamed: D__IRQ4.1 (K), RNL5_1_2.7 (R2.2)
unnamed: D__PSEL1.1 (K), RNL5_2_1.8 (R1.2)
unnamed: D__RD1.1 (K), RNL5_2_1.7 (R2.2)
unnamed: D__RESET1.1 (K), RNL5_1_1.6 (R3.2)
unnamed: D__STOP_CLK1.1 (K), RNL5_1_1.5 (R4.2)
unnamed: D__WR1.1 (K), RNL5_2_1.6 (R3.2)

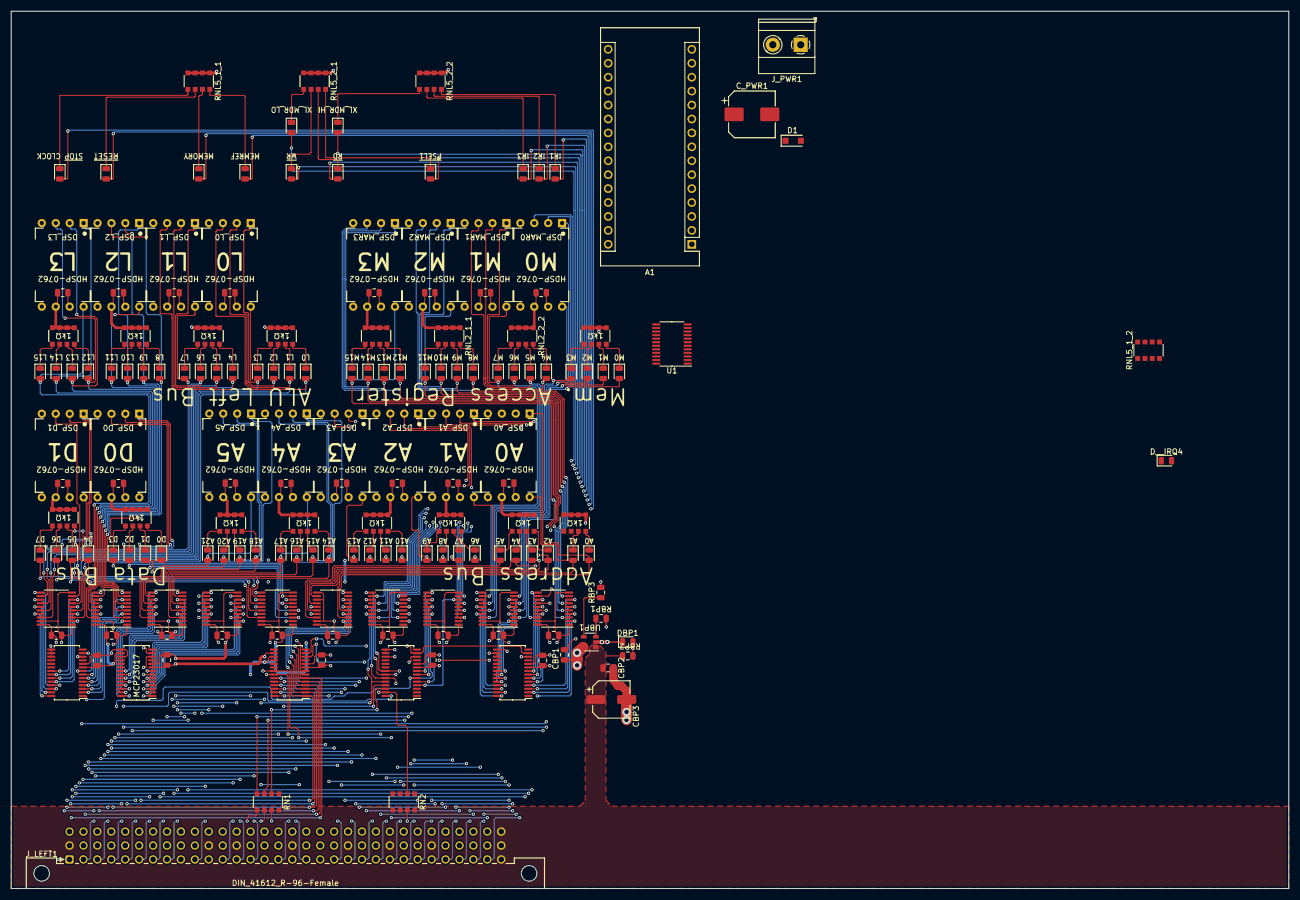
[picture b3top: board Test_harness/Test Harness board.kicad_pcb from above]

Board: 4 copper layers, 233.0 x 160.0 mm, 173 parts (0 on the bottom side), 240 nets.

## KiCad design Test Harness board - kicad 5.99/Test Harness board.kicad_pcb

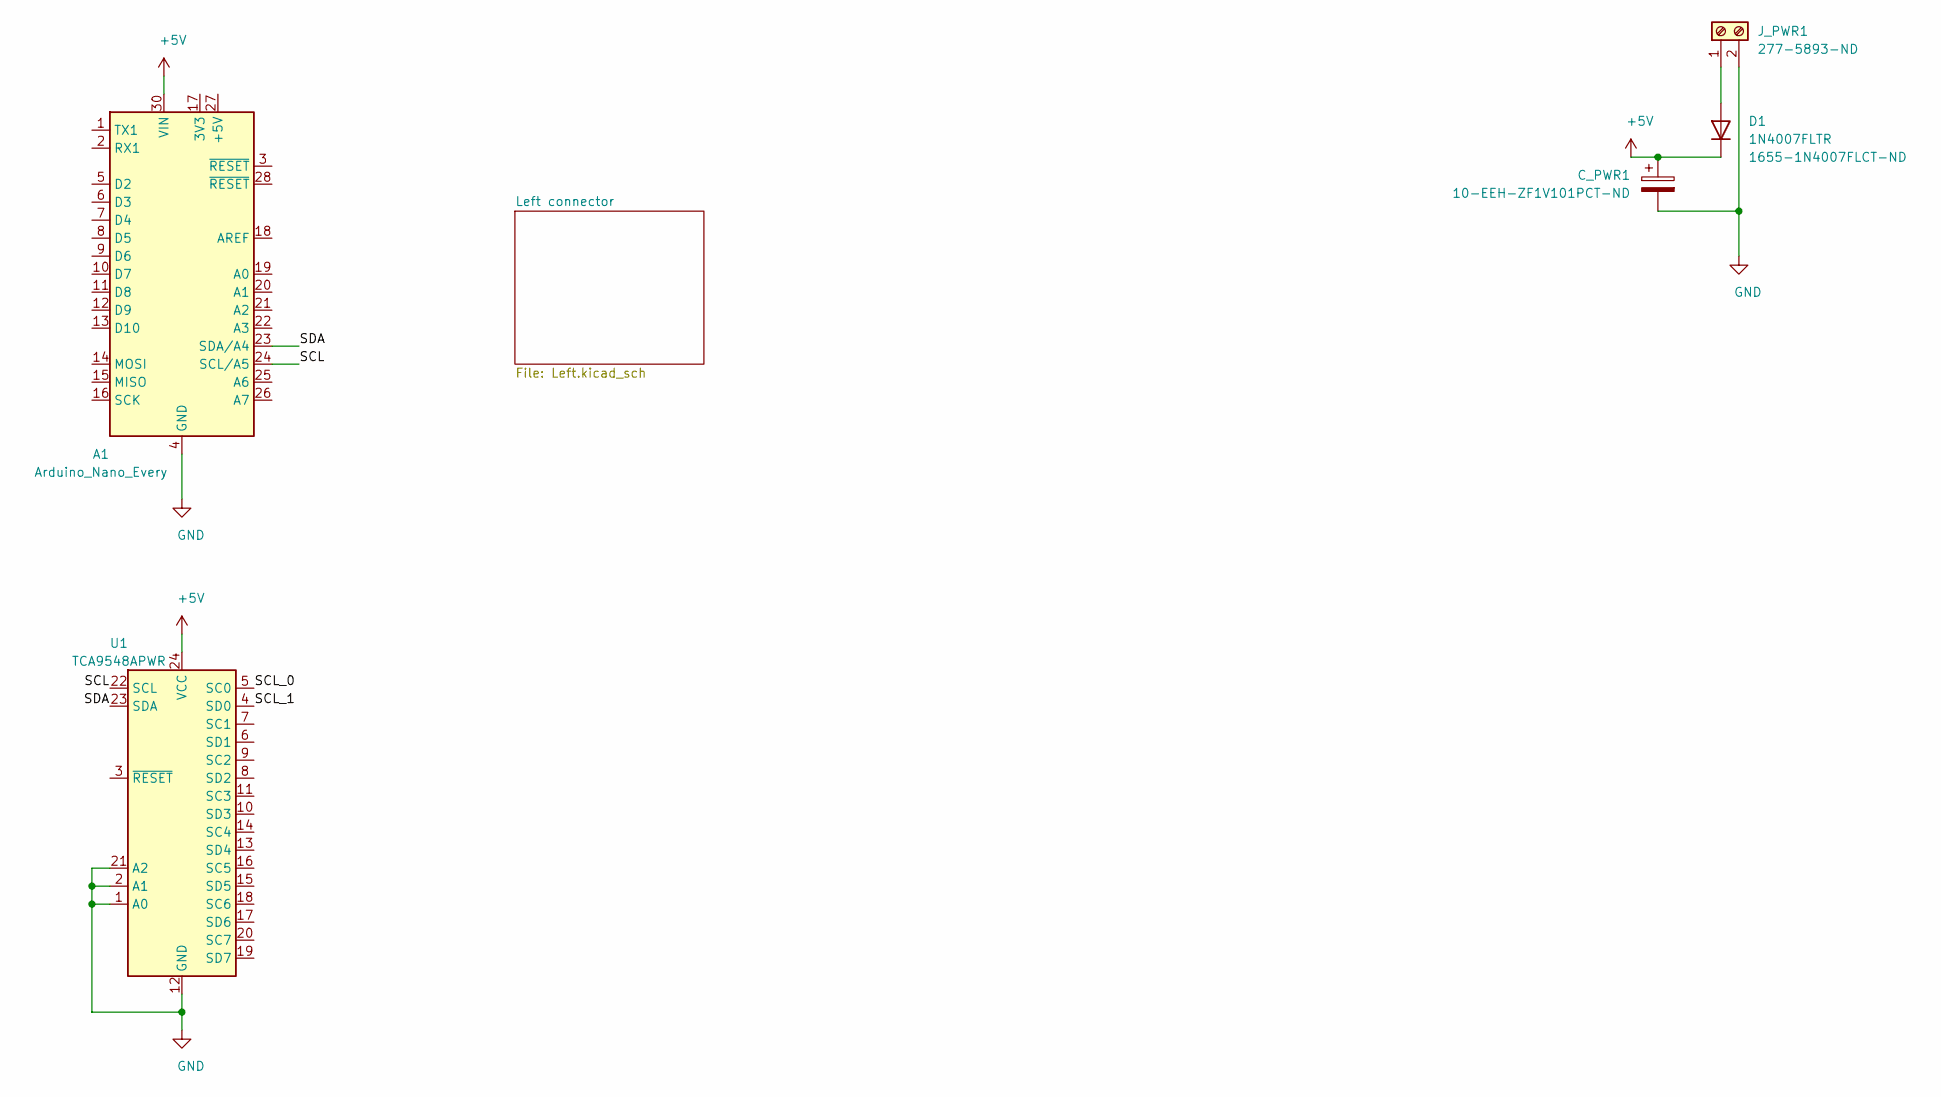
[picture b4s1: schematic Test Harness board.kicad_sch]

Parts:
A1: Arduino_Nano_Every; Arduino_Nano
C_PWR1: CP; CP_Elec_8x10; Digikey 10-EEH-ZF1V101PCT-ND
D1: 1N4007FLTR; D_SOD-123F; Digikey 1655-1N4007FLCT-ND
J_PWR1: Screw_Terminal_01x02; TerminalBlock_Phoenix_MKDS-1,5-2-5.08_1x02_P5.08mm_Horizont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; Digikey 277-5893-ND
U1: TCA9548APWR; TSSOP-24_4.4x7.8mm_P0.65mm

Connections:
+5V: A1.30 (VIN), C_PWR1.1, D1.1 (K), U1.24 (VCC); also elsewhere on the board
/SCL: A1.24 (SCL/A5), U1.22 (SCL)
/SCL_0: U1.5 (SC0)
/SCL_1: U1.4 (SD0)
/SDA: A1.23 (SDA/A4), U1.23 (SDA)
GND: A1.4 (GND), A1.29 (GND), C_PWR1.2, J_PWR1.2, U1.1 (A0), U1.2 (A1), U1.12 (GND), U1.21 (A2); also elsewhere on the board
unnamed: D1.2 (A), J_PWR1.1
